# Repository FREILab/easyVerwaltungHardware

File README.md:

# easyVerwaltung Hardware

Firmware und Dokumentation für die **easyVerwaltung**-Hardware des FREILab. Das System steuert Maschinenzugang, Nutzungsprotokollierung und Sicherheit via RFID-Authentifizierung gegen das easyVerwaltung-Backend.

---

## Hardware-Übersicht

### RFID-Box — Maschinenfreigabe

| Projekt | Hardware | API | Status |
|---|---|---|---|
| [RFID_BOX_legacy](firmware/projects/RFID_BOX_legacy/) | ESP32 Dev1 | Legacy | Stabil — [v1.0.0](https://github.com/FREILab/easyVerwaltungHardware/releases/tag/rfid-box-legacy%2Fv1.0.0) |
| [RFID_BOX_easyVerwaltung](firmware/projects/RFID_BOX_easyVerwaltung/) | ESP32 Dev1 | easyVerwaltung | Getestet — Server noch nicht in Production |

### Tür-Steuerung

| Projekt | Hardware | API | Status |
|---|---|---|---|
| [DOOR_legacy](firmware/projects/DOOR_legacy/) | Arduino UNO R4 WiFi | Legacy | Scheduled for Deletion |
| [DOOR_legacy_ESPArdu](firmware/projects/DOOR_legacy_ESPArdu/) | RobotDyn UNO+WiFi R3 (ATmega328P + ESP8266) | Legacy | Stabil — [v1.0.0](https://github.com/FREILab/easyVerwaltungHardware/releases/tag/door-legacy-espardu%2Fv1.0.0) |
| [DOOR_easyVerwaltung](firmware/projects/DOOR_easyVerwaltung/) | Arduino UNO R4 WiFi | easyVerwaltung | In Entwicklung |

### Lasersaur HMI

| Projekt | Hardware | API | Status |
|---|---|---|---|
| [LASERSAUR_HMI_legacy](firmware/projects/LASERSAUR_HMI_legacy/) | Arduino Mega + Ethernet-Shield | Legacy | Stabil (nicht mit neuem Server getestet) — wird durch ESPArdu ersetzt |
| [LASERSAUR_HMI_ESPArdu](firmware/projects/LASERSAUR_HMI_ESPArdu/) | Mega2560 WiFi R3 (ATmega2560 + ESP8266) | Legacy | Implementiert, noch nicht getestet |
| [LASERSAUR_HMI_easyVerwaltung](firmware/projects/LASERSAUR_HMI_easyVerwaltung/) | Arduino Giga R1 | easyVerwaltung | In Entwicklung |

### Machine Node

| Projekt | Hardware | API | Status |
|---|---|---|---|
| [MachineNode_legacy](firmware/projects/MachineNode_legacy/) | ESP32-S3-WROOM-1-N16R8 | Legacy | Stabil |
| [MachineNode_easyVerwaltung](firmware/projects/MachineNode_easyVerwaltung/) | ESP32-S3-WROOM-1-N16R8 | easyVerwaltung | Geplant |

---

## Repository-Struktur

```
firmware/
  projects/          # Firmware-Targets (je ein PlatformIO-Projekt)
  shared/
    easyAPI/         # Gemeinsame Backend-Kommunikation (HTTP/JSON)
```

Jedes Projekt in `projects/` enthält eine eigene `README.md` mit Hardware-Details, DIP-Belegung, Flash-Anleitung und Debugging-Hinweisen.

---

## Einrichtung

### Voraussetzungen

- Python ≥ 3.8
- PlatformIO Core (`pip install platformio`)

### Credentials

Jedes Projekt benötigt eine `platformio.secrets.ini` (nicht in Git). Vorlage liegt als `.example`-Datei bei:

```bash
cp platformio.secrets.ini.example platformio.secrets.ini
# Datei befüllen, dann:
pio run
```

Details zu den Feldern stehen in der jeweiligen Projekt-README.

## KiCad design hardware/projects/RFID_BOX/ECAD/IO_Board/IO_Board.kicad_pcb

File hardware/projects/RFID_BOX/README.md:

# Machine Node / RFID_BOX

> **Sicherheit geht vor Kosten, Baugröße und Bauteilzahl.** Das Gerät
> schaltet Netzspannung in einer Werkstatt, in der ungeschulte Personen
> daneben stehen. Wo Ziele kollidieren, gewinnt die Sicherheit.
>
> Vier Festlegungen sind bindend und werden nicht aufgeweicht:
>
> - Die Barriere Netz ↔ SELV beträgt **8 mm Luft- und Kriechstrecke** und
>   wird nicht auf den Normwert von 5 mm reduziert. Maßgeblich sind die
>   Bauteile, die sie queren, nicht das Minimum der Norm.
> - Bauteile über der Barriere brauchen **verstärkte oder doppelte
>   Isolierung** bei 250 V Arbeitsspannung. Eine hohe Prüfspannung in kV
>   allein genügt nicht — sie sagt über die Isolationsklasse nichts aus.
> - **Ein Einzelfehler darf nicht nach außen wirken.** Neue Schaltungsteile
>   werden gegen die [FMEA](FMEA.md) geprüft, bevor sie ins Layout gehen.
> - **Beim geöffneten Gerät ist nichts Netzführendes berührbar.** Feste
>   Abdeckplatten über dem I/O-Board geben nur die Feldterminals und den
>   Sicherungshalter frei. Das RFID-Board führt kein 230 V und darf
>   angefasst werden.
>
> Breiten, Abstände und Domänen stehen in
> [Layoutregeln.md](Layoutregeln.md), die Anforderungen in
> [Anforderungen.md](Anforderungen.md). Wo das Gerät teuer ist und was eine
> Alternative kosten würde, führt [Kostenoptimierung.md](Kostenoptimierung.md)
> mit — keine der Positionen dort hebt eine der vier Festlegungen auf.
> Material- und Leiterplattenkosten je Board stehen in [Kosten.md](Kosten.md).

## Einleitung

Dies ist der **RFID Node**: ein kompaktes Steuergerät, das elektrische
Geräte und Maschinen in der Werkstatt (z.B. Standfräse, Drehmaschine, FKS)
per RFID-Karte freischaltet. Er prüft die Karte einer Nutzerin oder eines
Nutzers gegen easyVerwaltung, gibt bei gültiger Berechtigung die Maschine
frei und schaltet sie beim Stopp oder bei Kartenentzug wieder ab.

Technisch besteht der Node aus zwei Platinen — I/O-Board mit Netzteil und
Schaltausgang, RFID-Board mit Controller, Bedienoberfläche und
RFID-Frontend — ergänzt um optionale Erweiterungsboards für Maschinen mit
zusätzlichem Bedarf.

## Aufbau

Das Gehäuse ist 3D-gedruckt und staubdicht ausgeführt. Display und
LED-Streifen sind von aussen sichtbar und durch eine Plexiglasscheibe
geschützt; der Streifen selbst sitzt innerhalb des Gehäuses. Der Stopp-Knopf
ist von aussen erreichbar.

Das Display sitzt nicht auf der Platine, sondern in einem eigenen
3D-gedruckten Träger, der von innen hinter die Plexiglasscheibe geklippt
wird. Die Verbindung zum RFID-Board läuft über das FPC des Displays.

Die Mechanik — Gehäuse, Display-Träger, Abdeckplatten — lebt in Fusion, nicht
in diesem Repo. Von dort kommen auch die Platinenumrisse als DXF
(`PCB_outline/`).

Die beiden Platinen sitzen in verschiedenen Gehäusehälften: das
**RFID-Board am Deckel**, das **I/O-Board an der unteren Schale**. Verbunden
werden sie über ein **Kabel** — für einen Board-to-Board-Stecker ist der
Abstand zu groß. Der Deckel hängt beim Öffnen damit am Kabel.

Alle Kabel werden einseitig über Kabeldurchführungen ins Gehäuse geführt,
von links nach rechts: Netz-Eingang 230 V, Schaltausgang (geschaltete 230 V
oder Steuerleitung für ein externes Schütz), optionale Notaus-Schleife,
optionales Extension-I/O. Nicht verwendete Durchführungen werden
verschlossen.

### Berührschutz

Das Gerät wird im Servicefall geöffnet, während es unter Umständen noch am
Netz hängt. Deshalb:

- Über dem I/O-Board sitzen **fest installierte, 3D-gedruckte
  Abdeckplatten**. Sie geben nur die Feldterminals und den Sicherungshalter
  frei — beide sind berührsichere Bauformen (WAGO Hebelklemme, WR-FSH mit
  Shocksafe PC2/IP20). Alles andere Netzführende bleibt abgedeckt.
- Die Platten sind kein Deckel, der beim Öffnen mitkommt: sie bleiben am
  Board bzw. am Gehäuseunterteil und lassen sich nur mit Werkzeug lösen.
- **Das RFID-Board führt kein 230 V** und darf im geöffneten Zustand
  berührt werden. Das ist eine bindende Randbedingung — es darf kein
  netzführendes Netz auf dieses Board wandern.

Alle Boards werden **lackiert**, damit Sägemehl und Feuchtigkeit über die
Lebensdauer keine Kriechpfade bilden. Vom Lack ausgenommen bleiben
Feldterminals, Sicherungskontakte und die Steckverbinder. Der Lack
ersetzt keine Abstände: Kriech- und Luftstrecken werden bemessen, als wäre
kein Lack vorhanden.

## Elektronik

Zwei Leiterplatten, in verschiedenen Gehäusehälften:

- **RFID-Board (im Deckel):** ESP32-S3, NFC-Controller CLRC663 mit der
  RFID-Antenne, Display, LED-Streifen, Buzzer, Stopp-Taster und eine
  USB-C-Buchse für Erstprogrammierung und Debug. MCU- und RFID-Teil lagen früher getrennt
  und sind zusammengelegt.
- **I/O-Board (in der unteren Schale):** 230-V-Netz, Schaltausgang und die
  Extension-Header.
  Hiervon gibt es **zwei getrennte Boards mit eigenem Layout**, von denen
  pro Gerät genau eines bestückt wird:
  - **I/O-Board 230V** — Lastrelais und Lastmessung zum direkten Schalten
    von Lasten bis 8 A.
  - **I/O-Board 24V** — potentialfreier Kontakt für ein externes Schütz.
    Ohne Lastpfad und Lastmessung, dadurch deutlich einfacher und ohne
    Bedarf an 70 µm Kupfer.

  Beide haben denselben Formfaktor und denselben Kabelstecker zum
  RFID-Board.

Dazu kommen zwei optionale, steckbare Erweiterungsboards auf dem I/O-Board:

- **Extension Board:** generisches Zusatzboard mit zwei Bestückvarianten —
  **NAMUR** (zwei optoisolierte Ausgänge, ein galvanisch getrennter Eingang)
  oder **Digital-I/O** (noch nicht spezifiziert). Ein Node trägt höchstens
  eine Variante.
- **E-Stop Extension Board:** Relais (24 V / 100 mA), dessen Kontakt in die
  Notaus-/Interlock-Schleife oder Bremsversorgung der Maschine eingeschleift
  wird. Fail-safe: stromlos = Schleife unterbrochen. Es öffnet bei Stopp
  oder Kartenentzug sofort, während die Hauptversorgung erst nach der
  Nachlaufzeit trennt.

## Energieversorgung

Die gesamte Versorgung kommt aus dem Netz-Eingang 230 V auf dem I/O-Board
und teilt sich dort in zwei Pfade:

- **Lastpfad (nur I/O-Board 230V):** Netz-Eingang → Ausgangssicherung (F300)
  → Lastrelais (K300) → Schaltausgang. Der Shunt (R307) liegt im
  **N-Rückweg vor dem Relais**, damit die Messung unabhängig vom
  Schaltzustand betriebsbereit bleibt. K300 trennt L und N gemeinsam, weil
  die N/L-Zuordnung an der Werkstatt-Steckdose nicht garantiert eindeutig
  ist.
- **Steuerpfad:** Netz-Eingang → Sicherung F302 → Gleichtaktdrossel (L300) →
  Y-Kondensatorpaar (C305/C308, Mittelabgriff an PE) → isoliertes
  AC/DC-Modul (U300, 24 V) → Regler auf 5 V (U302). Über das Kabel geht nur
  die 5-V-Schiene zum RFID-Board; **die 3,3 V erzeugt jede Platine selbst** —
  IC304 auf dem I/O-Board für die Eingangsseite des Isolators, IC102 auf dem
  MCU-Board für ESP32, NFC-Frontend und Display. Der DC-DC im Isolator zieht
  seinen Strom damit lokal und nicht über 30 cm Kabel. Die 24-V-Schiene
  versorgt die Relaisspule und geht zusätzlich über J302 Pin 2 (J102 Pin 13)
  für beleuchtete Taster zum RFID-Board; zur Überwachung geht außerdem ein
  Teilersignal (V24_SENSE) hinüber. LED-Leiste und Buzzer laufen direkt auf 5 V.
- **USB-C:** Das RFID-Board lässt sich auch allein über USB versorgen. VBUS
  (D401) und die 5 V vom Kabel (D100) laufen über je eine Schottky-Diode SS14
  auf +5V; keine Quelle speist in die andere zurück. Die Schiene liegt damit
  rund 0,4 V unter 5 V — für den 74AHCT125 (min. 4,5 V) knapp ausreichend.

Die **Lastmessung** liegt auf Netzpotential. Versorgung und UART laufen über
den Digitalisolator U301 (ISOW7721) mit integriertem DC-DC-Wandler, gespeist
aus der SELV-Seite — die Insel führt keinen eigenen Netzzweig. Über `ISO_EN`
nimmt die Firmware der Insel die Versorgung und startet das Mess-IC U303 neu.

Die Erweiterungsboards stecken auf dem I/O-Board und werden aus dem
Steuerpfad versorgt;
ihre Feldseite bleibt galvanisch getrennt und wird extern gespeist.

PE wird unverändert vom Netz-Eingang zum Schaltausgang durchgeschleift und
trägt den Mittelabgriff von C305/C308. Das Gehäuse ist Kunststoff, es gibt
keine Gehäusemasse.

**Sicherungen.** Die Lastausgangssicherung (F300) ist gesockelt und nach dem
Öffnen des Gehäuses ohne Löten tauschbar; eine Ersatzsicherung wird im
Gehäuse mitgeführt. Die Gerätesicherung (F302) ist als dokumentierte
Ausnahme fest verlötet (siehe [Anforderungen.md](Anforderungen.md), S5). Vor
F302 liegt R303, ein Sicherungswiderstand mit 10 Ω, der den Kurzschlussstrom
im Steuerzweig auf rund 25 A begrenzt — unter das Ausschaltvermögen von 35 A
der MRT.

**EMV.** Am Netz-Eingang liegen RV300 als Überspannungsschutz und C300 als
X2-Kondensator; eine Entladekette aus drei Widerständen bringt die
Steckerstifte in 0,17 s unter 60 V. Das Gleichtaktfilter aus L300 und
C305/C308 sitzt im Steuerzweig direkt vor U300, also an der Störquelle;
der Lastpfad trägt kein Filterbauteil. Auslegungspunkt ist 150 kHz bei 20 dB
Dämpfung. Drei Grenzen gelten dabei:

- Der Mittelabgriff nach PE ist zwingend — ohne ihn hat der Gleichtaktstrom
  im Kunststoffgehäuse keinen Rückweg, und die Drossel wirkt nur noch über
  ihre Streuinduktivität.
- Cy ist nach oben durch den Ableitstrom begrenzt; mehrere Nodes hängen am
  selben FI-Kreis.
- L nominal im Fenster 3–10 mH: nach unten setzt die Eckfrequenz die Grenze,
  nach oben die Eigenresonanz der Drossel.

**Bewusst nicht vorhanden:** eine Kontakt-Schutzbeschaltung am Lastrelais —
der Node ist Lastschalter, das Entkoppeln der Lastgeräte vom Netz ist nicht
seine Aufgabe. Eine Einschaltstrombegrenzung im Lastpfad — den Anlauf
tragen die träge Ausgangssicherung und das Einschaltvermögen von K300
(30 A, AgCdO-Kontakte). Ein thermisch geschützter Varistor (ThermoFuse) vor
RV300 (nicht wirtschaftlich), auftrennbare Netzbrücken (Platzbedarf) und
dedizierte Testpunkte (bei den Bauteilgrößen und PCBite nicht nötig).

## Signalfluss

Der Signalfluss beginnt an der RFID-Karte und endet am Schaltausgang. Vier
Aussagen, die man kennen muss:

- Der Stopp-Taster wirkt **nur über die Firmware** auf den ESP32. Einen
  hardwareseitigen Bypass gibt es nicht, weder am E-Stop-Relais noch am
  Relaistreiber der Hauptversorgung.
- Das Enable bleibt vollständig auf der SELV-Seite. Die Relaisspule hängt an
  der isolierten 24-V-Schiene und wird von **zwei Schaltern in Reihe**
  geführt: Low-Side-NMOS (Q301) und High-Side-PMOS (Q300) an getrennten
  GPIOs. Beide gehen im Ruhezustand sicher auf, und ein durchlegierter
  Schalter lässt sich über den anderen noch abschalten.
- Die Hauptversorgung wird ausschliesslich vom ESP32 nach Ablauf der
  Nachlaufzeit abgeschaltet; das E-Stop-Relais öffnet sofort.
- Die Isolationsbarriere quert nur die UART der Lastmessung, über U301 — er
  führt zugleich die Versorgung der Insel hinüber.

```mermaid
flowchart TB
    Antenne([RFID-Antenne])
    NFC["NFC-Controller CLRC663<br/>[3V3]"]
    ESP["ESP32<br/>[3V3]"]
    STOP["Stopp-Taster<br/>[3V3]"]
    TREIBER["Relaistreiber<br/>Low-Side NMOS + High-Side PMOS<br/>Gate [3V3] / Spule [24V]"]
    REL["Lastrelais<br/>Spule [24V] / Kontakt [230V]"]
    OUT([Terminal: Schaltausgang])

    MESS["Lastmessung<br/>Steuerseite<br/>Signal [3V3_ISO], netzbezogen"]
    OPTO_FB["Digitalisolator<br/>UART und Versorgung der Insel"]

    EXT["Extension Board<br/>[5V]"]
    ESTOP["E-Stop Relais<br/>[5V]"]
    OLED["OLED (ggf.)<br/>[3V3]"]

    Antenne -->|RF-Feld| NFC
    NFC -->|SPI| ESP
    ESP -->|Enable| TREIBER
    TREIBER -->|Ansteuerung| REL
    REL --> OUT

    STOP -->|I/O| ESP

    MESS <-->|UART| OPTO_FB
    OPTO_FB <-->|UART, isoliert| ESP

    ESP -->|I/O| EXT
    ESP -->|Enable| ESTOP
    ESP -->|I2C| OLED

    classDef term230 fill:#1565c0,color:#fff,stroke:#0d47a1
    classDef part230 fill:#ff9800,color:#000,stroke:#e65100
    classDef partSELV fill:#81c784,color:#000,stroke:#2e7d32
    classDef iso fill:#fff,color:#000,stroke:#6a1b9a,stroke-width:3px
    classDef touch230 fill:#fdd835,color:#000,stroke:#f57f17

    class OUT term230
    class REL part230
    class Antenne,NFC,ESP,STOP,EXT,ESTOP,OLED,TREIBER partSELV
    class MESS touch230
    class OPTO_FB iso
```

Abgerundet = Terminal oder Eingabe, eckig = Funktionsblock. Grün =
Kleinspannung, orange = 230-V-führend, blau = 230-V-Terminal, gelb =
Signalpegel isoliert, Bauteil berührt aber die Netzseite, weiss mit
violettem Rahmen = Isolationsbarriere. `[…]` nennt den Signalpegel.

## Kernbauteile

Nur die Teile, die das Gerät bestimmen. Dazu die Sicherung: **im Servicefall
wird nur sie getauscht**, alles andere ist fest verlötet. Denkbar wäre noch
das Display, das über sein FPC steckbar ist.

Die vollständige Liste steht im Schaltplan und in
`ECAD/IO_Board/IO_Board.csv`, die Preise in `MyCSLib/KiCad/parts_db.json`.

| Funktion | Hersteller / Teilenummer | Warum dieser |
|---|---|---|
| Mikrocontroller | Espressif<br>ESP32-S3-WROOM-1-N16R8 | WLAN/BLE, 16 MB Flash, 8 MB PSRAM |
| Lastrelais (K300) | TE Connectivity<br>T92S11D12-24 | 2-polig (N+L), 30 A Einschaltvermögen, verstärkte Isolation Spule/Kontakt 8 mm / 9,5 mm / 4 kVrms. Bauhöhe 30,7 mm |
| Potentialfreier Kontakt, E-Stop (K2, K3) | Omron<br>G5V-1-2 DC24 | 100 mA / 24 V, Spule 24 V |
| Display | EastRising<br>ER-TFT020-3 | 2" IPS, 240×320, 4-Wire SPI. Ersetzt das DT010ATFT bei gleichem Bustyp, 5,3-fache aktive Fläche. Nacktes Panel, Anschluss über steckbares FPC 14-pol / 0,5 mm |
| Lastausgangssicherung + Ersatz (F300) | Bel Fuse<br>5HT 10-R | 10 A / 250 V träge, Keramik sandgefüllt, **Ausschaltvermögen 1500 A**. Die Glasrohrtype mit 100 A reicht nicht. Die VDE-Lizenz der Baureihe deckt nur 1–6,3 A, die 10 A laufen über UL, CSA und CCC |
| Gerätesicherung (F302) | Bel Fuse<br>MRT 500-BULK | 500 mA / 250 V träge, IEC 60127-3. Fest verlötet, dokumentierte Ausnahme zu S5 |

## TODO

- **Delta-Review I/O-Board (Marc Ihle):** Alle 9 Punkte aus
  [Review_IO_Board.md](Review_IO_Board.md) umgesetzt, Exporte erzeugt und
  Rückmeldung in [Review_Marc_Ihle.xlsx](Review/Review_Marc_Ihle.xlsx)
  eingetragen — bereit zur Delta-Review.
- **Review RFID-Board (Marc Ihle) abarbeiten:** 15 offene Punkte dokumentiert
  in [Review_RFID_Board.md](Review_RFID_Board.md) (noch nichts umgesetzt) —
  insbesondere Wichtigkeit 4: `SPI-MOSI`/`SCK` aus dem Spulenbereich über die
  `GND`-Plane ziehen (#10), sowie Wichtigkeit 3: Stroko zwischen `D400` und
  ESP `IC100A` (#3) und TVS-Diode an `VBUS`/`D401` (#4).
- **Zweiten Taster neben dem Stopp-Taster vorsehen:** zweiten Taster am
  Gehäuse neben dem Stopp-Taster einplanen und auf dem RFID-Board mit
  Anschluss (z. B. J101 erweitern oder separater Header), Beschaltung analog
  `STOP` (Pull-up, Serienwiderstand, Entprell-Kondensator) und freiem
  ESP32-GPIO (z. B. GPIO 15) anbinden. Für ggf. beleuchtete 24-V-Taster liegt
  `+24V` bereits an `J102` Pin 13 (`J302` Pin 2) an.
- **Verbindungskabel (FFC, J102 ↔ J302) — PFLICHTPUNKT RFID-Board-BOM:**
  Dummy-Bauteil für das Kabel GCT `10-14-x-xxxx-C-4-08-4-T` auf dem
  **RFID-Board** in die BOM aufnehmen (nicht vergessen!); Länge in Fusion
  bestimmen. Kontaktseite voraussichtlich Typ A (beide Enden gleiche Seite):
  J302 ist um 180° gedreht, damit das Kabel ohne Verdrehung Pin n auf Pin
  15−n legt und die Padreihen beider Stecker auf derselben Seite liegen.
  Gegen die Amphenol-Zeichnung prüfen. Pads 15/16 (Lötlaschen) des SFW14S
  haben keinen Pin im Symbol.

### Offen aus der Bauteilplanung

- **Piezo PKLCS1212E40A1-R1 ist bei Digi-Key Last Time Buy** (Mouser 27.236
  Stück). Alternative mit aktivem Status wäre `CMT-1203-SMT-TR` von Same
  Sky — dafür ohne fertiges KiCad-Footprint und 3 dB leiser.
- **Quarz Y200:** das Symbol hat zwei Pins, das Footprint vier Pads. Die
  beiden Gehäusepads bleiben ohne Netz. Sollen sie auf GND, muss der Master
  von `Device:Crystal_GND24` kommen.
- **I/O-Board 24V zeichnen:** zwei potentialfreie Kontakte für externes
  Hauptschütz und Aux-Ausgang. Die Kontakte müssen den Einschaltstrom einer
  Schützspule tragen — ein Signalrelais wie das G5V-1 reicht dafür nicht.
  Der Haupt-Kontakt braucht dieselbe Verriegelung aus zwei Schaltern wie
  K300, für Aux genügt ein Low-Side-Schalter. Beide Kontakte müssen
  zusätzlich **12 V DC / 2 A** schalten können.
- **PDF-Erstellung beschleunigen:** Tool bzw. Setup für Schaltplan-, Layout-
  und Doku-PDFs und den Bau der Review-Pakete; das Erzeugen dauert bisher
  jedes Mal lange.
- **`aux_en` und `EXT_IO`** auf dem I/O-Board beschalten (E-Stop- bzw.
  Extension-Header); sie enden derzeit an J302.
- **Stopp-Taster auswählen** (Panel-Mount im Gehäuse, angeschlossen an J101).
- **`antenna/README.md` nachziehen:** dort stehen C₀ mit 50 V und
  R<sub>S</sub> mit 2,4 Ω im 0603, bestückt sind 100 V und 2,49 Ω im 1206.
- **Anforderung A1 nachziehen:** aus dem LED-Ring mit zwölf LEDs ist eine
  Leiste über dem Display mit **sieben** LEDs geworden, dazu kommt die
  Statusliste.

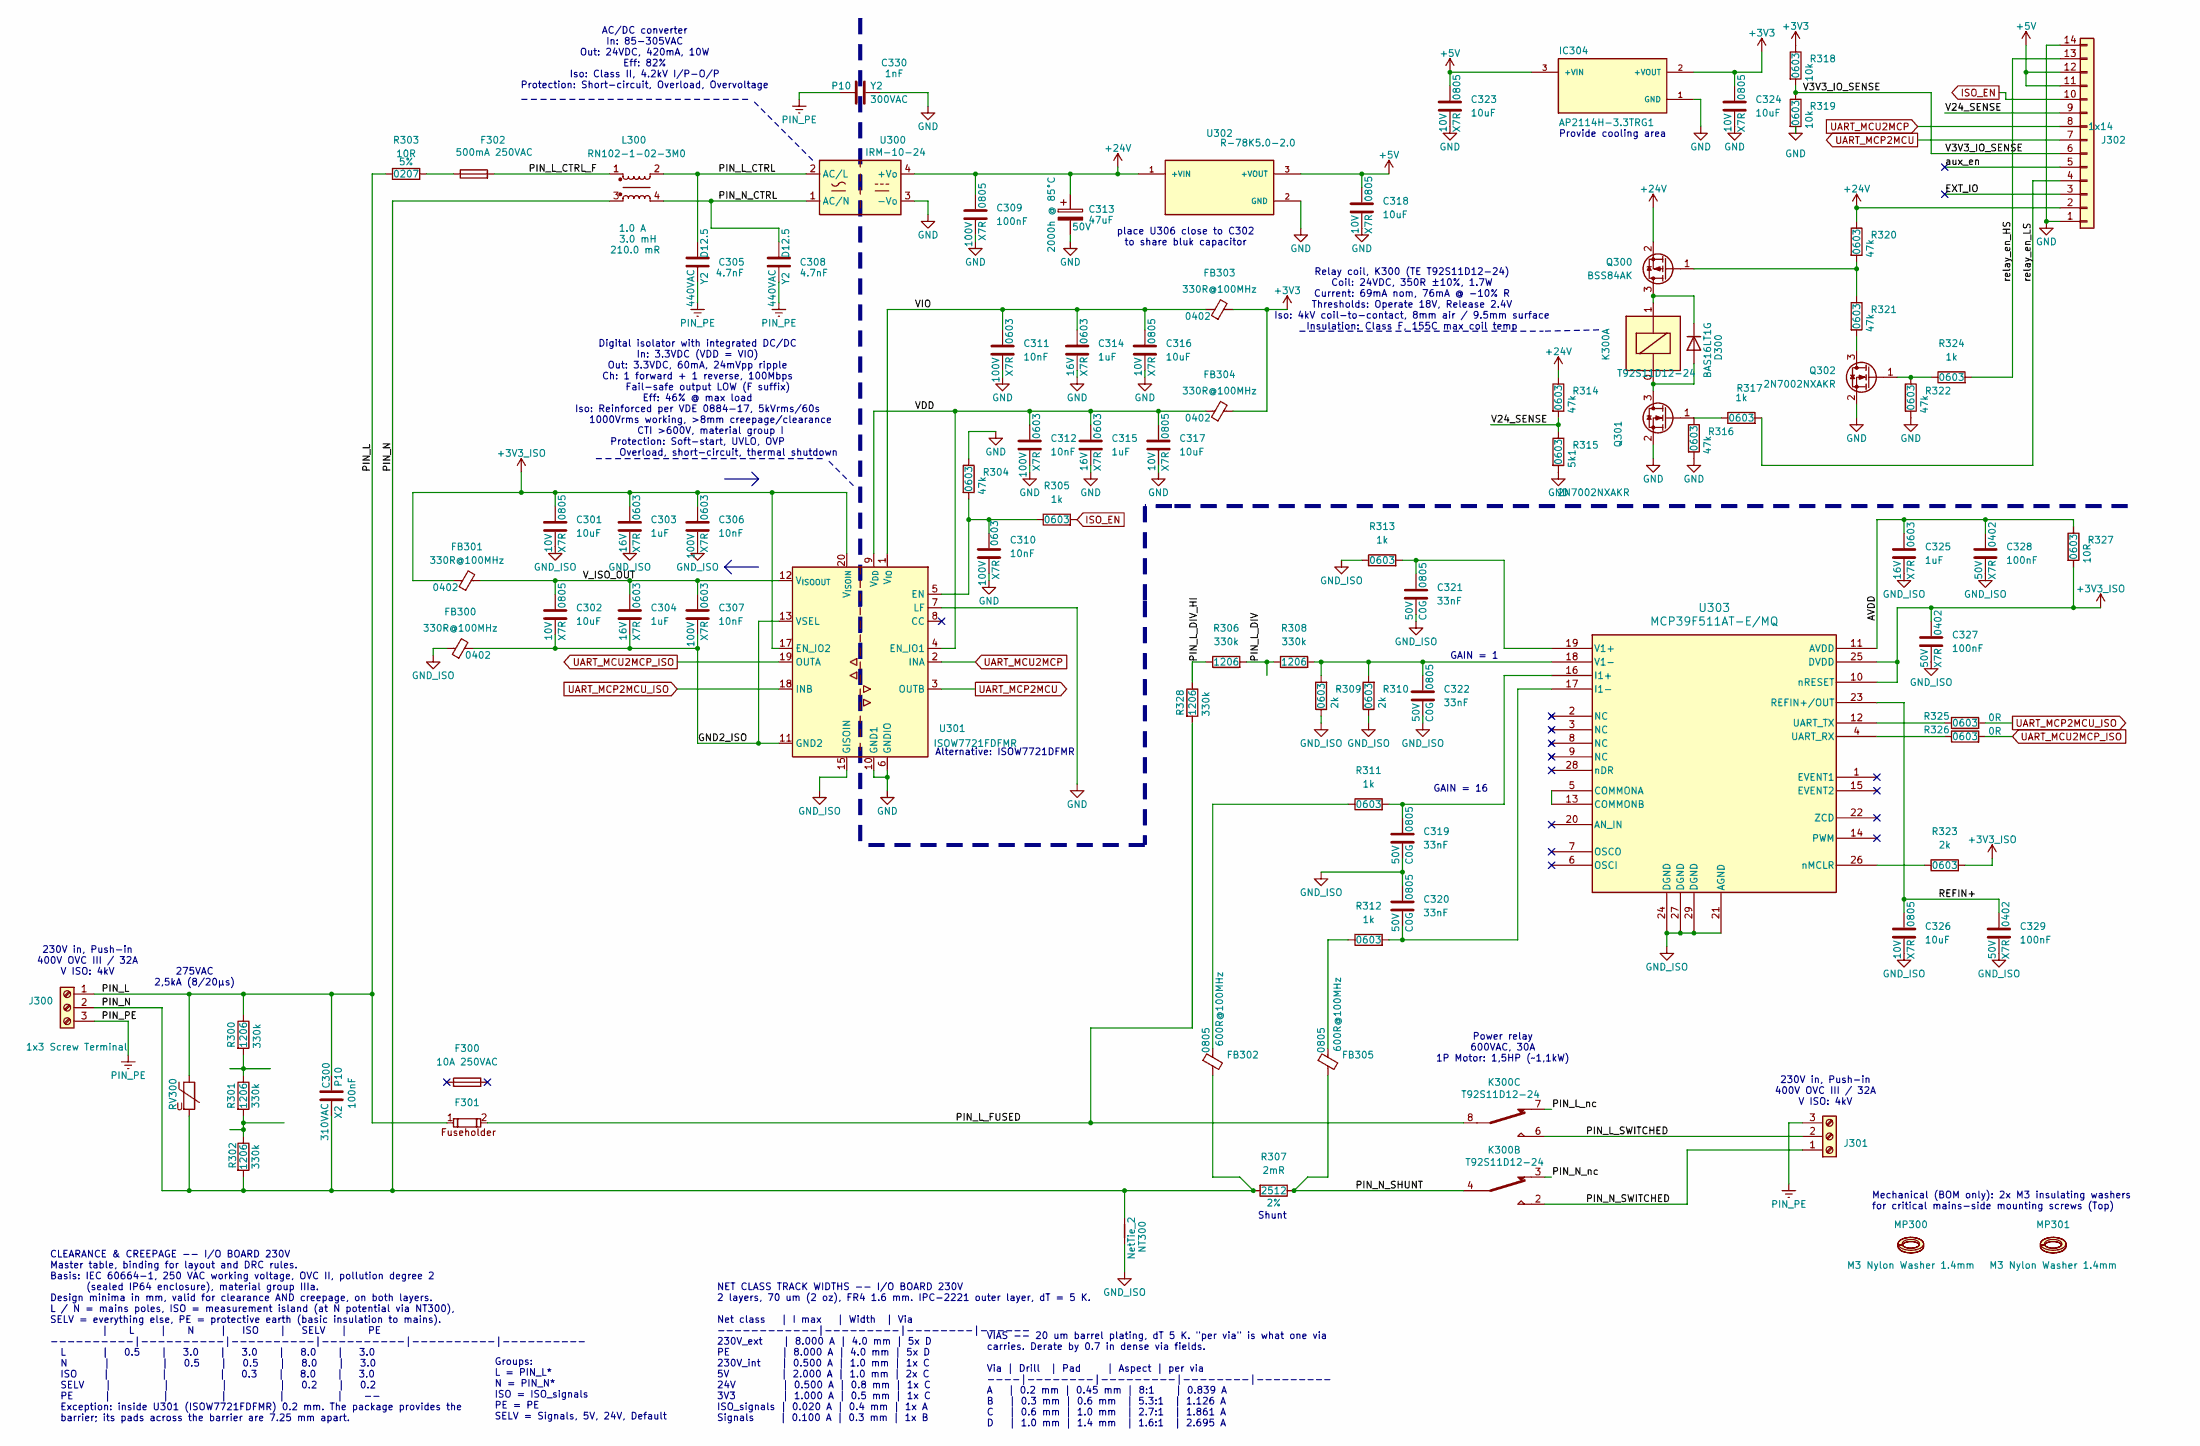
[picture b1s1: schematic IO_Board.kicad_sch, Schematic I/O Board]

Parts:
C300: 100nF; C_Wurth_WCAP-FTXX-P10L13W7H13; Voltage Rating 310VAC; Manufacturer Part Number 890334023023CS
C301, C302, C316, C317, C318, C323, C324, C326: 10uF; C_0805_2012Metric; Voltage Rating 10V; Manufacturer Part Number CC0805KFX7R6BB106
C303, C304, C314, C315, C325: 1uF; C_0603_1608Metric; Voltage Rating 16V; Manufacturer Part Number CGA3E1X7R1C105K080AC
C305, C308: 4.7nF; C_Disc_D12.5mm_W5.0mm_P7.50mm; Voltage Rating 440VAC; Manufacturer Part Number VY2472M49Y5US63L7
C306, C307, C310, C311, C312: 10nF; C_0603_1608Metric; Voltage Rating 100V; Manufacturer Part Number GRM188R72A103KA01D
C309: 100nF; C_0805_2012Metric; Voltage Rating 100V; Manufacturer Part Number 885012207128
C313: 47uF; CP_Radial_D6.3mm_H11.0mm_P2.50mm; Voltage Rating 50V; Manufacturer Part Number 860010673012
C319, C320, C321, C322: 33nF; C_0805_2012Metric; Voltage Rating 50V; Manufacturer Part Number GRM2165C1H333JA01J
C327, C328, C329: 100nF; C_0402_1005Metric; Voltage Rating 50V; Manufacturer Part Number GCM155R71H104KE02J
C330: 1nF; C_Rect_L13.5mm_W4.0mm_P10.00mm_FKS3_FKP3_MKS4; Voltage Rating 300VAC; Manufacturer Part Number 890404123001CS
D300: BAS16LT1G; SOT-23; Manufacturer Part Number BAS16LT1G
F300: 10A 250VAC; Voltage Rating 250VAC; Manufacturer Part Number 5HT 10-R
F301: F_696309001002; F_Wurth_WR-FSH_696309001002; Manufacturer Part Number 696309001002
F302: 500mA 250VAC; F_MRT_BEL; Voltage Rating 250VAC; Manufacturer Part Number MRT 500-BULK
FB300, FB301, FB303, FB304: 330R@100MHz; L_0402_1005Metric; Manufacturer Part Number BLM15EX331SN1D
FB302, FB305: 600R@100MHz; L_0805_2012Metric; Manufacturer Part Number MH2029-601Y
IC304: AP2114H-3.3TRG1; SOT-223-3_TabPin2; Manufacturer Part Number AP2114H-3.3TRG1
J300, J301: 1x3 Screw Terminal; J_2604-1103_WAG; Manufacturer Part Number 2604-1103
J302: 1x14; J_01x14_SFW14S-2STE1LF; Manufacturer Part Number SFW14S-2STE1LF
K300: T92S11D12-24; K_T92S11D12-24; Manufacturer Part Number T92S11D12-24
L300: RN102-1-02-3M0; L_RN102_SCN; Manufacturer Part Number RN102-1-02-3M0
MP300, MP301: M3 Nylon Washer 1.4mm; Manufacturer Part Number 16MLSW030070070
NT300: NetTie_2
Q300: BSS84AK; SOT-23; Manufacturer Part Number BSS84AK,215
Q301, Q302: 2N7002NXAKR; SOT-23; Manufacturer Part Number 2N7002NXAKR
R300, R301, R302, R306, R308, R328: 330k; R_1206_3216Metric; Tolerance 1%; Manufacturer Part Number CRCW1206330KFKEAHP
R303: 10R; R_Axial_DIN0207_L6.3mm_D2.5mm_P5.08mm_Vertical; Tolerance 5%; Manufacturer Part Number PR01000101009JA500
R304, R314, R316, R320, R321, R322: 47k; R_0603_1608Metric; Tolerance 1%; Manufacturer Part Number CRCW060347K0FKEAC
R305, R311, R312, R313, R317, R324: 1k; R_0603_1608Metric; Tolerance 1%; Manufacturer Part Number CRCW06031K00FKEAC
R307: 2mR; R_2512_CSI2H-2512K-2L00G; Tolerance 2%; Manufacturer Part Number CSI2H-2512K-2L00G
R309, R310, R323: 2k; R_0603_1608Metric; Tolerance 1%; Manufacturer Part Number CRCW06032K00FKEAC
R315: 5k1; R_0603_1608Metric; Tolerance 1%; Manufacturer Part Number CRCW06035K10FKEA
R318, R319: 10k; R_0603_1608Metric; Tolerance 1%; Manufacturer Part Number CRCW060310K0FKEAC
R325, R326: 0R; R_0603_1608Metric; Tolerance 1%; Manufacturer Part Number CRCW06030000Z0EBC
R327: 10R; R_0603_1608Metric; Tolerance 1%; Manufacturer Part Number CRCW060310R0FKEA
RV300: RVAR_B72210S0271K101; RV_Disc_D12mm_W5.1mm_P7.5mm; Manufacturer Part Number B72210S0271K101
U300: IRM-10-24; IC_IRM-10-24_THT; Manufacturer Part Number IRM-10-24
U301: ISOW7721FDFMR; SOIC-20W_7.5x12.8mm_P1.27mm; Manufacturer Part Number ISOW7721FDFMR
U302: R-78K5.0-2.0; IC_CONV_R-78K5.0-2.0; Manufacturer Part Number R-78K5.0-2.0
U303: MCP39F511AT-E/MQ; IC_QFN28_MQ_MCH; Manufacturer Part Number MCP39F511AT-E/MQ

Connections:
+3V3: C324.1, FB303.2, FB304.2, IC304.2 (+VOUT), R318.1
+3V3_ISO: C301.1, C303.1, C306.1, C327.1, FB301.1, R323.2, R327.2, U301.17 (EN_IO2), U301.20 (V_{ISOIN}), U303.10 (nRESET), U303.25 (DVDD)
+5V: C318.1, C323.1, IC304.3 (+VIN), J302.11, J302.12, U302.3 (+VOUT)
+24V: C309.1, C313.1, J302.2, Q300.2 (S), R314.1, R320.1, U300.4 (+Vo), U302.1 (+VIN)
/AVDD: C325.1, C328.1, R327.1, U303.11 (AVDD)
/EXT_IO: J302.3
/GND2_ISO: C302.2, C304.2, C307.2, FB300.2, U301.11 (GND2), U301.13 (VSEL)
/PIN_L: C300.1, F301.1, J300.1, J300.4, R300.1, R303.1, RV300.1
/PIN_L_CTRL: C305.1, L300.2, U300.2 (AC/L)
/PIN_L_CTRL_F: F302.2, L300.1
/PIN_L_DIV: R306.2, R308.1
/PIN_L_DIV_HI: R306.1, R328.1
/PIN_L_FUSED: F301.2, K300.8, R328.2
/PIN_L_SWITCHED: J301.2 (Pin_3), J301.5, K300.6
/PIN_L_nc: K300.7
/PIN_N: C300.2, FB302.2, J300.2 (Pin_3), J300.5, L300.3, NT300.2, R302.2, R307.2, RV300.2
/PIN_N_CTRL: C308.1, L300.4, U300.1 (AC/N)
/PIN_N_SHUNT: FB305.2, K300.4, R307.1
/PIN_N_SWITCHED: J301.1, J301.4, K300.2
/PIN_N_nc: K300.3
/REFIN+: C326.1, C329.1, U303.23 (REFIN+/OUT)
/V3V3_IO_SENSE: J302.6, R318.2, R319.1
/V24_SENSE: J302.9, R314.2, R315.1
/VDD: C312.1, C315.1, C317.1, FB304.1, U301.4 (EN_IO1), U301.9 (V_{DD})
/VIO: C311.1, C314.1, C316.1, FB303.1, U301.1 (V_{IO})
/V_ISO_OUT: C302.1, C304.1, C307.1, FB301.2, U301.12 (V_{ISOOUT})
/aux_en: J302.5
/relay_en_HS: J302.13, R324.2
/relay_en_LS: J302.4, R317.2
GND: C309.2, C310.2, C311.2, C312.2, C313.2, C314.2, C315.2, C316.2, C317.2, C318.2, C323.2, C324.2, C330.2, IC304.1 (GND), J302.1, J302.14, Q301.2 (S), Q302.2 (S), R304.1, R315.2, R316.2, R319.2, R322.2, U300.3 (-Vo), U301.6 (GNDIO), U301.7 (LF), U301.10 (GND1), U302.2 (GND)
GND_ISO: C301.2, C303.2, C306.2, C319.2, C320.1, C321.2, C322.2, C325.2, C326.2, C327.2, C328.2, C329.2, FB300.1, NT300.1, R309.1, R310.1, R313.1, U301.15 (GISOIN), U303.21 (AGND), U303.24 (DGND), U303.27 (DGND), U303.29 (DGND)
ISO_EN: J302.10, R305.2
unnamed: D300.1 (A), K300.0, Q301.3 (D)
unnamed: D300.3 (K), K300.1, Q300.3 (D)
unnamed: F302.1, R303.2
unnamed: FB302.1, R311.1
unnamed: FB305.1, R312.1
unnamed: Q300.1 (G), R320.2, R321.1
unnamed: Q301.1 (G), R316.1, R317.1
unnamed: Q302.3 (D), R321.2
unnamed: Q302.1 (G), R322.1, R324.1
unnamed: R300.2, R301.1
unnamed: R301.2, R302.1
unnamed: C310.1, R304.2, R305.1, U301.5 (EN)
unnamed: U303.5 (COMMONA), U303.13 (COMMONB)
unnamed: C319.1, R311.2, U303.16 (I1+)
unnamed: C320.2, R312.2, U303.17 (I1-)
unnamed: R326.1, U303.4 (UART_RX)
unnamed: R325.1, U303.12 (UART_TX)
unnamed: C321.1, R313.2, U303.19 (V1+)
unnamed: C322.1, R308.2, R309.2, R310.2, U303.18 (V1-)
unnamed: R323.1, U303.26 (nMCLR)
PIN_PE: C305.2, C308.2, C330.1, J300.3, J300.6, J301.3, J301.6
UART_MCP2MCU: J302.7, U301.3 (OUTB)
UART_MCP2MCU_ISO: R325.2, U301.18 (INB)
UART_MCU2MCP: J302.8, U301.2 (INA)
UART_MCU2MCP_ISO: R326.2, U301.19 (OUTA)

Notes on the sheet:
VIAS -- 20 um barrel plating, dT 5 K. "per via" is what one via carries. Derate by 0.7 in dense via fields. Via | Drill | Pad | Aspect | per via ----|--------|---------|--------|--------- A | 0.2 mm | 0.45 mm | 8:1 | 0.839 A B | 0.3 mm | 0.6 mm | 5.3:1 | 1.126 A C | 0.6 mm | 1.0 mm | 2.7:1 | 1.861 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
230V in, Push-in 400V OVC III / 32A V ISO: 4kV
Groups: L = PIN_L* N = PIN_N* ISO = ISO_signals PE = PE SELV = Signals, 5V, 24V, Default
NET CLASS TRACK WIDTHS -- I/O BOARD 230V 2 layers, 70 um (2 oz), FR4 1.6 mm. IPC-2221 outer layer, dT = 5 K. Net class | I max | Width | Via ------------|---------|--------|------ 230V_ext | 8.000 A | 4.0 mm | 5x D PE | 8.000 A | 4.0 mm | 5x D 230V_int | 0.500 A | 1.0 mm | 1x C 5V | 2.000 A | 1.0 m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
place U306 close to C302 to share bluk capacitor
AC/DC converter In: 85-305VAC Out: 24VDC, 420mA, 10W Eff: 82% Iso: Class II, 4.2kV I/P-O/P Protection: Short-circuit, Overload, Overvoltage
Power relay 600VAC, 30A 1P Motor: 1,5HP (~1,1kW)
Alternative: ISOW7721DFMR
Digital isolator with integrated DC/DC In: 3.3VDC (VDD = VIO) Out: 3.3VDC, 60mA, 24mVpp ripple Ch: 1 forward + 1 reverse, 100Mbps Fail-safe output LOW (F suffix) Eff: 46% @ max load Iso: Reinforced per VDE 0884-17, 5kVrms/60s 1000Vrms working, >8mm creepage/clearance CTI >600V, material group I Pro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
275VAC 2,5kA (8/20µs)
CLEARANCE & CREEPAGE -- I/O BOARD 230V Master table, binding for layout and DRC rules. Basis: IEC 60664-1, 250 VAC working voltage, OVC II, pollution degree 2 (sealed IP64 enclosure), material group IIIa. Design minima in mm, valid for clearance AND creepage, on both layers. L / N = mains poles, IS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
Mechanical (BOM only): 2x M3 insulating washers for critical mains-side mounting screws (Top)
GAIN = 16
Relay coil, K300 (TE T92S11D12-24) Coil: 24VDC, 350R ±10%, 1.7W Current: 69mA nom, 76mA @ -10% R Thresholds: Operate 18V, Release 2.4V Iso: 4kV coil-to-contact, 8mm air / 9.5mm surface Insulation: Class F, 155C max coil temp
Shunt
GAIN = 1
Provide cooling area

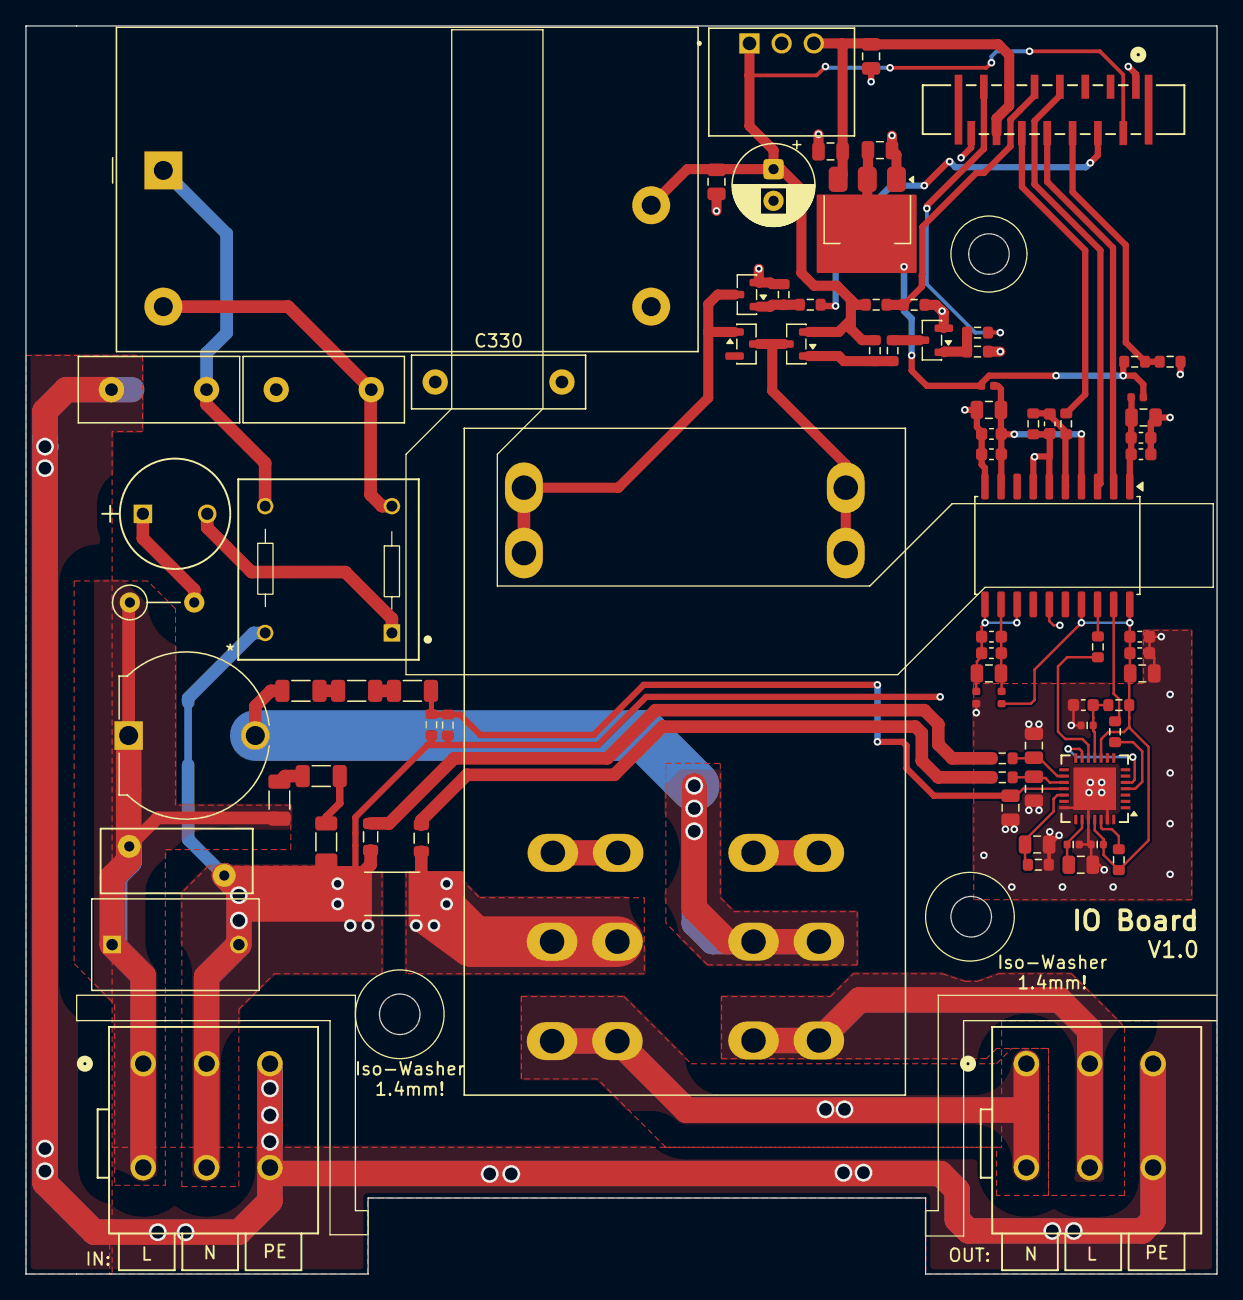
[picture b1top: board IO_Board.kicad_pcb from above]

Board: 2 copper layers, 94.0 x 98.5 mm, 85 parts (1 on the bottom side), 53 nets.

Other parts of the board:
LOGO300: Logo_FREILab_24mm

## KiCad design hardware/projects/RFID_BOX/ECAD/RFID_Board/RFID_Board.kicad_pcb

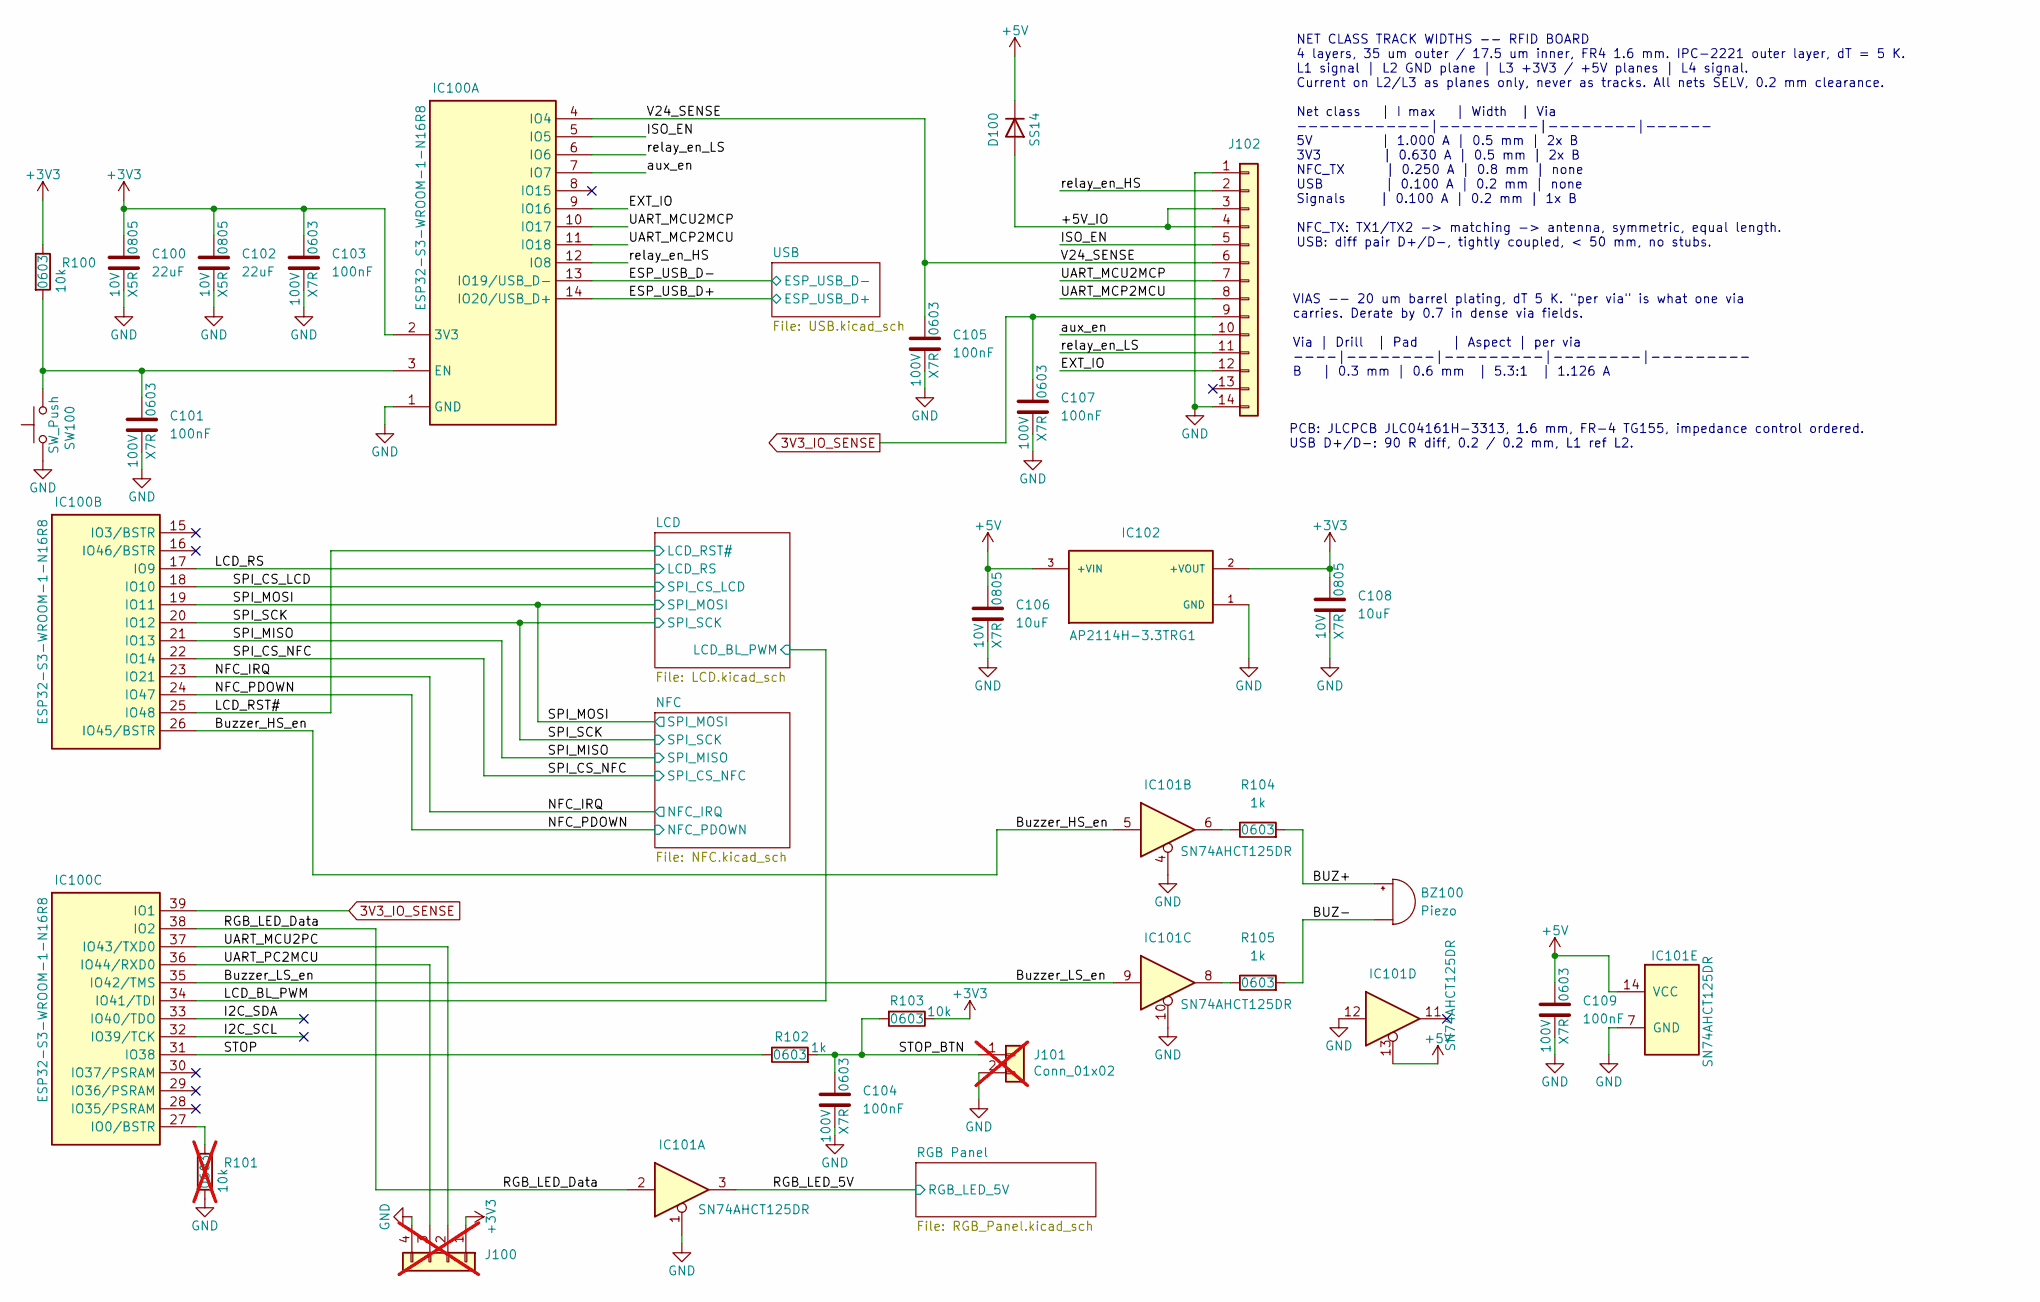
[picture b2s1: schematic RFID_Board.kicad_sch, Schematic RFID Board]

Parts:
BZ100: Piezo; Buzzer_Murata_PKLCS1212E; Manufacturer Part Number PKLCS1212E40A1-R1
C100, C102: 22uF; C_0805_2012Metric; Voltage Rating 10V; Manufacturer Part Number GRM21BR61A226ME51K
C101, C103, C104, C105, C107, C109: 100nF; C_0603_1608Metric; Voltage Rating 100V; Manufacturer Part Number 885012206120
C106, C108: 10uF; C_0805_2012Metric; Voltage Rating 10V; Manufacturer Part Number CC0805KFX7R6BB106
D100: SS14; D_SMA; Manufacturer Part Number SS14
IC100: ESP32-S3-WROOM-1-N16R8; IC_ESP32S3WROOM1N16R8; Manufacturer Part Number ESP32-S3-WROOM-1-N16R8
IC101: SN74AHCT125DR; SOIC-14_3.9x8.7mm_P1.27mm; Manufacturer Part Number SN74AHCT125DR
IC102: AP2114H-3.3TRG1; SOT-223-3_TabPin2; Manufacturer Part Number AP2114H-3.3TRG1
J100: Conn_01x04; PinHeader_1x04_P2.54mm_Vertical; not fitted
J101: Conn_01x02; PinHeader_1x02_P2.54mm_Vertical; not fitted
J102: 1x14; J_01x14_SFW14S-2STE1LF; Manufacturer Part Number SFW14S-2STE1LF
R100, R103: 10k; R_0603_1608Metric; Tolerance 1%; Manufacturer Part Number CRCW060310K0FKEAC
R101: 10k; R_0603_1608Metric; Tolerance 1%; Manufacturer Part Number CRCW060310K0FKEAC; not fitted
R102, R104, R105: 1k; R_0603_1608Metric; Tolerance 1%; Manufacturer Part Number CRCW06031K00FKEAC
SW100: SW_Push; SW_SPST_TL3305A; Manufacturer Part Number TL3305AF160QG

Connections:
3V3_IO_SENSE: C107.1, IC100.39 (IO1), J102.9
+3V3: C100.1, C102.1, C103.1, C108.1, IC100.2 (3V3), IC102.2 (+VOUT), J100.1, R100.1, R103.1; also elsewhere on the board
+5V: C106.1, C109.1, D100.1 (K), IC101.13, IC101.14 (VCC), IC102.3 (+VIN); also elsewhere on the board
/+5V_IO: D100.2 (A), J102.3, J102.4
/BUZ+: BZ100.1 (+), R104.2
/BUZ-: BZ100.2 (-), R105.2
/Buzzer_HS_en: IC100.26 (IO45/BSTR), IC101.5
/Buzzer_LS_en: IC100.35 (IO42/TMS), IC101.9
/ESP_USB_D+: IC100.14 (IO20/USB_D+); also elsewhere on the board
/ESP_USB_D-: IC100.13 (IO19/USB_D-); also elsewhere on the board
/EXT_IO: IC100.9 (IO16), J102.12
/I2C_SCL: IC100.32 (IO39/TCK)
/I2C_SDA: IC100.33 (IO40/TDO)
/ISO_EN: IC100.5 (IO5), J102.5
/LCD_BL_PWM: IC100.34 (IO41/TDI); also elsewhere on the board
/LCD_RS: IC100.17 (IO9); also elsewhere on the board
/LCD_RST#: IC100.25 (IO48); also elsewhere on the board
/NFC_IRQ: IC100.23 (IO21); also elsewhere on the board
/NFC_PDOWN: IC100.24 (IO47); also elsewhere on the board
/RGB_LED_5V: IC101.3; also elsewhere on the board
/RGB_LED_Data: IC100.38 (IO2), IC101.2
/SPI_CS_LCD: IC100.18 (IO10); also elsewhere on the board
/SPI_CS_NFC: IC100.22 (IO14); also elsewhere on the board
/SPI_MISO: IC100.21 (IO13); also elsewhere on the board
/SPI_MOSI: IC100.19 (IO11); also elsewhere on the board
/SPI_SCK: IC100.20 (IO12); also elsewhere on the board
/STOP: IC100.31 (IO38), R102.1
/STOP_BTN: C104.1, J101.1, R102.2, R103.2
/UART_MCP2MCU: IC100.11 (IO18), J102.8
/UART_MCU2MCP: IC100.10 (IO17), J102.7
/UART_MCU2PC: IC100.37 (IO43/TXD0), J100.2
/UART_PC2MCU: IC100.36 (IO44/RXD0), J100.3
/V24_SENSE: C105.1, IC100.4 (IO4), J102.6
/aux_en: IC100.7 (IO7), J102.10
/relay_en_HS: IC100.12 (IO8), J102.2
/relay_en_LS: IC100.6 (IO6), J102.11
GND: C100.2, C101.2, C102.2, C103.2, C104.2, C105.2, C106.2, C107.2, C108.2, C109.2, IC100.1 (GND), IC100.40 (GND), IC100.41 (GND), IC100.42 (GND), IC100.43 (GND), IC100.44 (GND), IC100.45 (GND), IC100.46 (GND), IC100.47 (GND), IC100.48 (GND), IC100.49 (GND), IC101.1, IC101.4, IC101.7 (GND), IC101.10, IC101.12, IC102.1 (GND), J100.4, J101.2, J102.1, J102.14, R101.2, SW100.1; also elsewhere on the board
unnamed: C101.1, IC100.3 (EN), R100.2, SW100.2
unnamed: IC100.27 (IO0/BSTR), R101.1
unnamed: IC101.6, R104.1
unnamed: IC101.8, R105.1

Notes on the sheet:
PCB: JLCPCB JLC04161H-3313, 1.6 mm, FR-4 TG155, impedance control ordered. USB D+/D-: 90 R diff, 0.2 / 0.2 mm, L1 ref L2.
VIAS -- 20 um barrel plating, dT 5 K. "per via" is what one via carries. Derate by 0.7 in dense via fields. Via | Drill | Pad | Aspect | per via ----|--------|---------|--------|--------- B | 0.3 mm | 0.6 mm | 5.3:1 | 1.126 A
NET CLASS TRACK WIDTHS -- RFID BOARD 4 layers, 35 um outer / 17.5 um inner, FR4 1.6 mm. IPC-2221 outer layer, dT = 5 K. L1 signal | L2 GND plane | L3 +3V3 / +5V planes | L4 signal. Current on L2/L3 as planes only, never as tracks. All nets SELV, 0.2 mm clearance. Net class | I max | Width | Via ---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

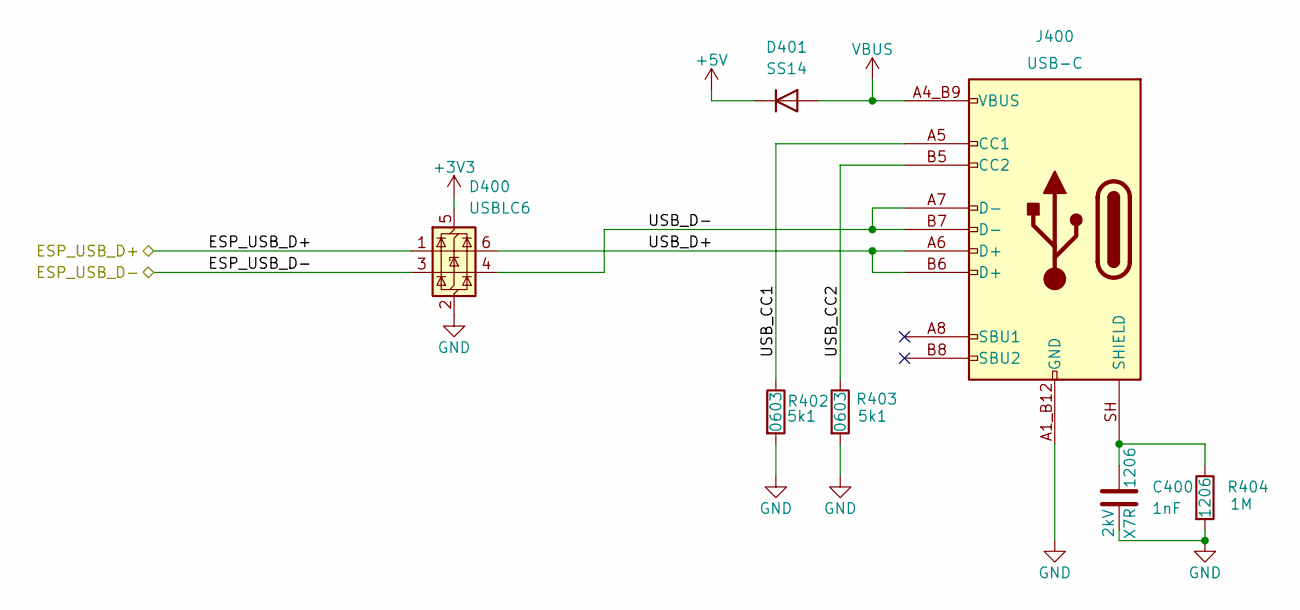
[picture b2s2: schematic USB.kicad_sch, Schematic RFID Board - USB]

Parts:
C400: 1nF; C_1206_3216Metric; Voltage Rating 2kV; Manufacturer Part Number 885342208024
D400: USBLC6; SOT-23-6; Manufacturer Part Number USBLC6-2SC6Y
D401: SS14; D_SMA; Manufacturer Part Number SS14
J400: USB-C; J_USB-C_USB4105-GF-A; Manufacturer Part Number USB4105-GF-A
R402, R403: 5k1; R_0603_1608Metric; Tolerance 1%; Manufacturer Part Number CRCW06035K10FKEA
R404: 1M; R_1206_3216Metric; Tolerance 1%; Manufacturer Part Number CRCW12061M00FKEA

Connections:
+3V3: D400.5 (VBUS); also elsewhere on the board
+5V: D401.1 (K); also elsewhere on the board
/ESP_USB_D+: D400.1 (I/O1); also elsewhere on the board
/ESP_USB_D-: D400.3 (I/O2); also elsewhere on the board
/USB/USB_CC1: J400.A5 (CC1), R402.1
/USB/USB_CC2: J400.B5 (CC2), R403.1
/USB/USB_D+: D400.6 (I/O1), J400.A6 (D+), J400.B6 (D+)
/USB/USB_D-: D400.4 (I/O2), J400.A7 (D-), J400.B7 (D-)
GND: C400.2, D400.2 (GND), J400.A1_B12 (GND), J400.B1_A12 (GND), R402.2, R403.2, R404.2; also elsewhere on the board
unnamed: C400.1, J400.SH (SHIELD), R404.1
VBUS: D401.2 (A), J400.A4_B9 (VBUS), J400.B4_A9 (VBUS)
